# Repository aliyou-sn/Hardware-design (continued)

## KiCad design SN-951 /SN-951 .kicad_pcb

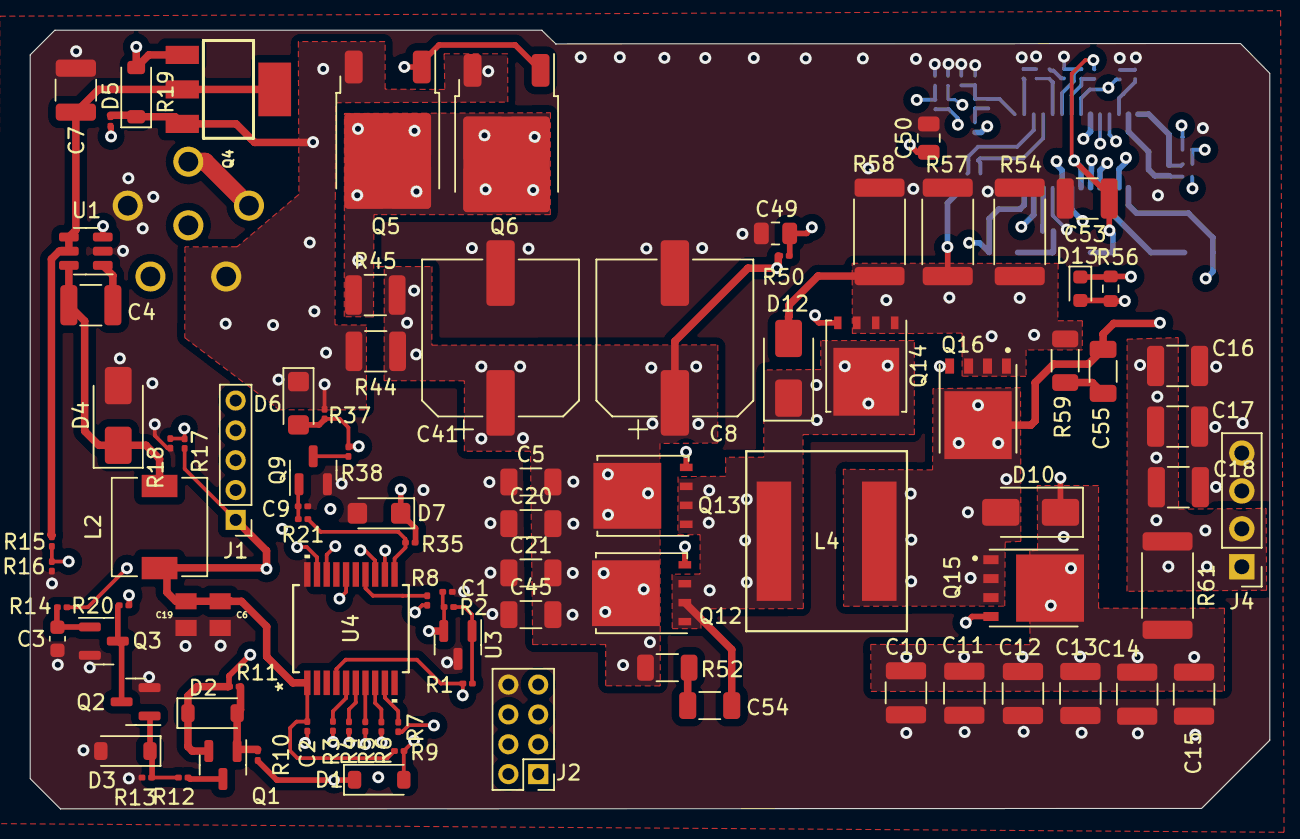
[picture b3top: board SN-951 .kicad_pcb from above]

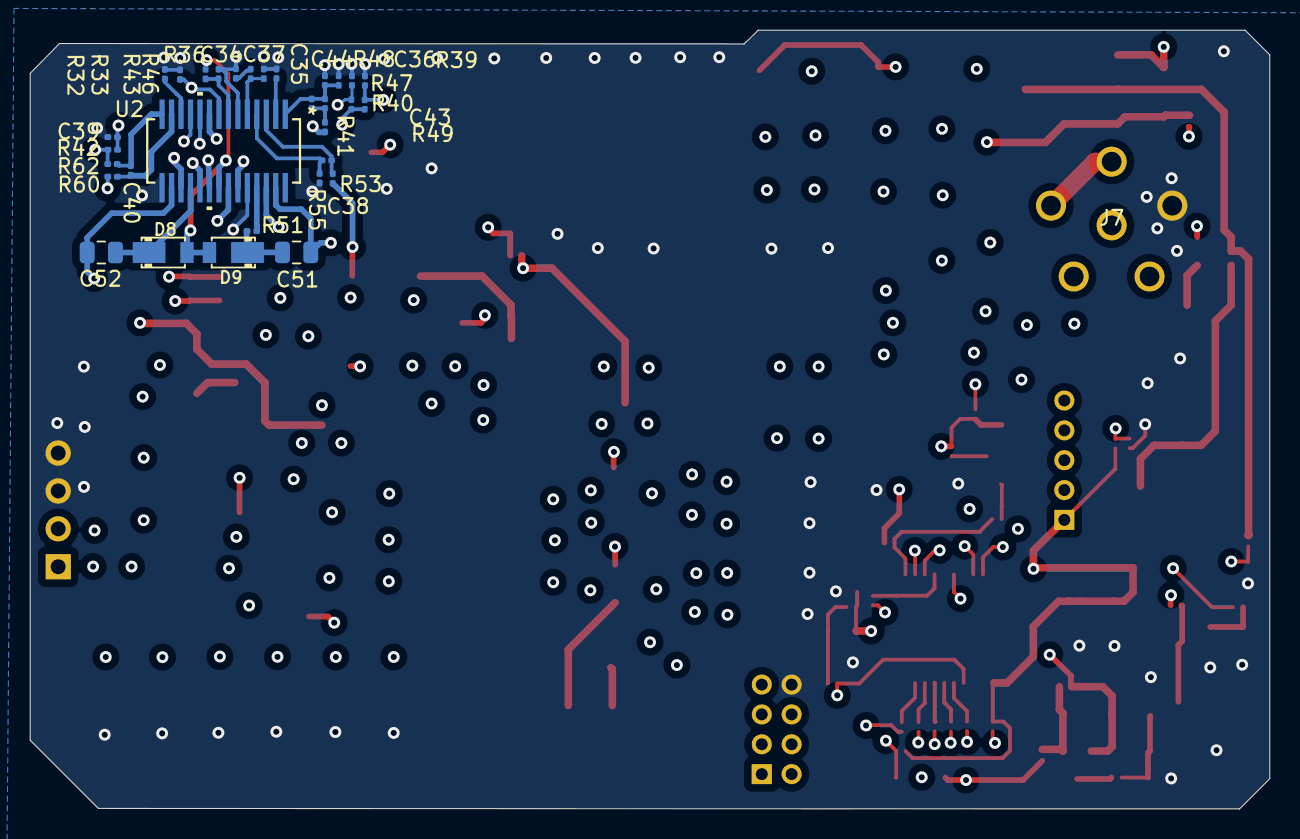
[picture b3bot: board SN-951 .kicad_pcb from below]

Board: 4 copper layers, 83.1 x 52.2 mm, 124 parts (32 on the bottom side), 74 nets.

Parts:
C1, C2, C36, C39: 100NF; C_0201_0603Metric
C3: 100NF; C_0603_1608Metric
C4: 150NF; C_1210_3225Metric
C5, C20, C21, C45: 3.3UF; C_1206_3216Metric
C6, C19: 22UF; CAPC2012X140N
C7, C53: 1UF; C_1210_3225Metric
C8, C41: 270UF; CP_Elec_10x7.7
C9: NI; C_0201_0603Metric
C10, C11, C12, C13, C14, C15, C16, C17, C18: 22UF; C_1210_3225Metric
C34: 10NF; C_0201_0603Metric
C35: 6.8NF; C_0201_0603Metric
C37: 100PF; C_0201_0603Metric
C38: 68PF; C_0201_0603Metric
C40: 2.2UF; C_0201_0603Metric
C43, C44: 1NF; C_0201_0603Metric
C49, C50: 1UF; C_0805_2012Metric
C51, C52: 220NF; C_0805_2012Metric
C54: 390PF; C_1206_3216Metric
C55: 1.8NF; C_1206_3216Metric
D1: 1N4148; D_SOD-123
D2, D3, D5: D_Zener; D_SOD-123
D4: B160-E3; D_SMA
D6, D7: BZD27Cxx; D_SMF
D8, D9: DFLS160-7; POWERDI-123
D10, D12: B340; D_SMA
D13: D; D_0603_1608Metric
J1: Conn_01x05; PinHeader_1x05_P2.00mm_Vertical
J2: Conn_01x08; PinHeader_2x04_P2.00mm_Vertical
J4: OUTPUT; PinHeader_1x04_P2.54mm_Vertical
J7: DIN-6; SC-C-179495_HEADER
L2: SRN6045-470M; L_6.3x6.3_H3
L4: 3uH; IND_XAL1010-152MED_COC
Q1: BSS84; SOT-23
Q2, Q3: 2N7002; SOT-23
Q4: NDT2955; SOT223
Q5, Q6: SUD50P04-08; TO-252-2
Q9: IRLML0030; SOT-23
Q12, Q13, Q14: BSC026N08NS5; TDSON-8-1
Q15, Q16: BSC010NE2LSI; TRANS_BSC010NE2LSI
R1, R16: 12K; R_0201_0603Metric
R2, R14: 750R; R_0201_0603Metric
R3, R4, R5, R6, R7, R8: 330R; R_0201_0603Metric
R9, R13, R15: 100K; R_0201_0603Metric
R10, R12: 1OK; R_0201_0603Metric
R11, R19: 20K; R_0201_0603Metric
R17: 5K49; R_0201_0603Metric
R18: 1K; R_0201_0603Metric
R20, R36: 10K; R_0201_0603Metric
R21, R33, R38, R40: NI; R_0201_0603Metric
R32, R43: 0R; R_0201_0603Metric
R35, R41, R42, R53, R55, R60, R62: 100R; R_0201_0603Metric
R37: R_0201_0603Metric
R39: 12k1; R_0201_0603Metric
R44, R45: R_1210_3225Metric
R46: 46K4; R_0201_0603Metric
R47: 113k; R_0201_0603Metric
R48: 8k06; R_0201_0603Metric
R49, R51: 10R; R_0201_0603Metric
R50: 15R; R_0201_0603Metric
R52: 5R6; R_1206_3216Metric
R54, R57, R58: 0R010; R_2512_6332Metric
R56: 0R; R_0603_1608Metric
R59: 3R6; R_1206_3216Metric
R61: 0R003; R_2512_6332Metric
U1: LMR14206; SOT-23-6
U2: LTC3789EGN-PBF; SSOP-28_GN_LIT
U3: MCP120-xxxxTT; SOT-23
U4: PIC16F720-I/SS; SSOP20_MC_MCH

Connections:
+BATT: D2.1 (K), D5.1 (K), D6.1 (K), J7.4, Q1.2 (S), Q4.3, Q5.3 (S), Q6.3 (S), R11.1, R19.1, R37.1, R44.1
/controller/RA0: J1.3, U4.19 (RA0/AN0/ICSPDAT)
/controller/RA1: J1.4, U4.18 (RA1/AN1/ICSPCLK)
/controller/RB4/: D1.1 (K), J2.1, R10.2
/controller/RC2: R8.1, U4.14 (RC2/AN6)
/controller/RC3: R5.1, U4.7 (RC3/AN7)
/controller/RC4: R4.1, U4.6 (RC4)
/controller/RC5: R3.1, U4.5 (RC5/CCP1)
/controller/RC6: R6.1, U4.8 (RC6/AN8/*SS)
/controller/RC7: R7.1, U4.9 (RC7/AN9/SDO)
/controller/V_BAT1: C7.2, Q4.2, Q4.4, R15.1, U1.4 (~SHDN), U1.5 (VIN)
/converter/BG2: D13.1 (K), R56.1, U2.19 (BG2)
/converter/INTVCC: C53.1, D8.A, D9.A, R32.2, U2.21 (INTVCC)
/converter/IOSENSE+: C40.2, R60.2, U2.13 (IOSENSE+)
/converter/IOSENSE-: C40.1, R62.2, U2.14 (IOSENSE-)
/converter/MODE: R32.1, R33.2, U2.7 (MODE/PLLIN)
/converter/RUN: D7.1 (K), R35.1, R39.2, R40.1, U2.9 (RUN)
/converter/SENSE+: C38.1, R53.2, U2.3 (SENSE+)
/converter/SENSE-: C38.2, R55.2, U2.4 (SENSE-)
/converter/TG2: Q15.4, U2.17 (TG2)
/converter/VIN: C49.1, R50.1, U2.22 (VIN)
GND: C1.1, C3.2, C5.1, C6.1, C7.1, C8.2, C9.1, C10.1, C11.1, C12.1, C13.1, C14.1, C15.1, C16.2, C17.2, C18.2, C19.1, C20.1, C21.1, C35.2, C36.2, C37.2, C39.1, C41.2, C44.2, C45.1, C49.2, C50.2, C53.2, D3.2 (A), D4.2 (A), D7.2 (A), J2.8, J4.3, J4.4, J7.2, Q2.2 (S), Q3.2 (S), Q9.2 (S), R13.2, R16.2, R18.2, R33.1, R36.1, R39.1, R43.2, R46.2, R48.1, R54.1, R55.1, R57.1, R58.1, U1.2 (GND), U2.6 (SGND), U2.15 (TRIM), U2.24 (PGND), U3.3 (VSS), U4.20 (VSS)
unnamed: C34.2, R36.2
unnamed: C43.1, R47.2, R49.2
unnamed: C51.2, D9.C, R51.1
unnamed: C54.1, R52.1
unnamed: C55.2, R59.2
unnamed: D1.2 (A), R9.1, U4.13 (RB4/AN10/SDI/SDA)
unnamed: D2.2 (A), Q1.1 (G), R10.1, R11.2
unnamed: D3.1 (K), Q2.1 (G), R12.1, R13.1
unnamed: C4.1, D4.1 (K), L2.2, U1.6 (SW)
unnamed: D5.2 (A), Q4.1, R19.2, R20.1
unnamed: D6.2 (A), Q5.1 (G), Q6.1 (G), R37.2, R38.1
unnamed: C52.2, C55.1, D10.2 (A), L4.2, Q15.1, Q15.2, Q15.3, Q16.5_8, U2.16 (SW2)
unnamed: C10.2, C11.2, C12.2, C13.2, C14.2, C15.2, D10.1 (K), Q15.5_8, R60.1, R61.2
unnamed: D12.2 (A), Q14.1 (S), Q14.2 (S), Q14.3 (S), Q16.1, Q16.2, Q16.3, R53.1, R54.2, R57.2, R58.2, R59.1
unnamed: C51.1, C54.2, D12.1 (K), L4.1, Q12.1 (S), Q12.2 (S), Q12.3 (S), Q13.1 (S), Q13.2 (S), Q13.3 (S), Q14.5 (D), U2.27 (SW1)
unnamed: D13.2 (A), Q16.4, R56.2
unnamed: C2.2, J1.2
unnamed: J1.5, R1.1, U4.4 (RA3/*MCLR/VPP)
unnamed: J2.2, R4.2
unnamed: J2.3, R5.2
unnamed: J2.4, R3.2
unnamed: J2.5, R6.2
unnamed: J2.6, R8.2
unnamed: J2.7, R7.2
unnamed: J7.1, J7.5
unnamed: Q5.2 (D), Q6.2 (D), R45.1
unnamed: Q1.3 (D), R12.2
unnamed: Q2.3 (D), Q3.3 (D), R20.2
unnamed: C3.1, Q3.1 (G), R14.1
unnamed: Q9.3 (D), R38.2
unnamed: C9.2, Q9.1 (G), R21.2
unnamed: Q12.4 (G), Q13.4 (G), U2.26 (TG1)
unnamed: Q14.4 (G), U2.23 (BG1)
unnamed: C4.2, U1.1 (CB)
unnamed: R17.2, R18.1, U1.3 (FB)
unnamed: R51.2, U2.25 (BOOST1)
unnamed: C52.1, D8.C, U2.18 (BOOST2)
unnamed: C50.1, U2.20 (EXTVCC)
unnamed: R46.1, U2.8 (FREQ)
unnamed: R43.1, U2.12 (ILIM)
unnamed: C34.1, C37.1, U2.5 (ITH)
unnamed: C35.1, U2.2 (SS)
unnamed: C43.2, C44.1, R47.1, R48.2, U2.1 (VFB)
unnamed: C36.1, R41.1, U2.10 (VINSNS)
unnamed: C39.2, R42.1, U2.11 (VOUTSNS)
unnamed: R1.2, R2.1, U3.1 (~RST)
unnamed: R14.2, U4.12 (RB5/AN11/RX/DT)
unnamed: R15.2, R16.1, U4.16 (RC0/AN4)
OUT-EN: R21.1, R35.2, U4.11 (RB6/SCK/SCL)
VCC: C1.2, C2.1, C6.2, C19.2, J1.1, L2.1, R2.2, R9.2, R17.1, U3.2 (VDD), U4.1 (VDD)
VDC: C16.1, C17.1, C18.1, J4.1, J4.2, R42.2, R49.1, R61.1, R62.1
VS: C5.2, C8.1, C20.2, C21.2, C41.1, C45.2, Q12.5 (D), Q13.5 (D), R40.2, R41.2, R44.2, R45.2, R50.2, R52.2
